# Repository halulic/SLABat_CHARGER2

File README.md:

Overview

This project is a smart charger for 12V SLA (Sealed Lead-Acid) batteries based on the ESP32 microcontroller.

The system monitors battery voltage, charging current, power, and temperature in real time and displays all important parameters on a TFT display.
Charging is controlled automatically to ensure safe and reliable battery charging.

⸻

Main Features
	•	Smart charging control for 12V SLA batteries
	•	ESP32 microcontroller
	•	Real-time monitoring of:
	•	Battery voltage
	•	Charging current
	•	Power consumption
	•	Temperature
	•	TFT display interface
	•	Automatic charge management
	•	MOSFET-based power control
	•	Protection and status indicators

⸻

Hardware

Main components used:
	•	ESP32 development board
	•	INA219 current/voltage sensors
	•	TFT display (ILI9341 / 3.2”)
	•	MOSFET switching stage
	•	NTC temperature sensor
	•	External power supply
	•	12V SLA battery

⸻

Display Information

The TFT display shows:
	•	Battery voltage
	•	Charging current
	•	Charging power
	•	Temperature
	•	Charging status
	•	System indicators

⸻

Applications
	•	Charging sealed lead-acid batteries
	•	Workshop battery maintenance
	•	DIY power electronics projects
	•	Educational electronics projects

⸻

Future Improvements

Possible future upgrades:
	•	Data logging
	•	WiFi monitoring
	•	Battery health estimation
	•	Charge cycle history

⸻

License

Open-source project for educational and DIY use.

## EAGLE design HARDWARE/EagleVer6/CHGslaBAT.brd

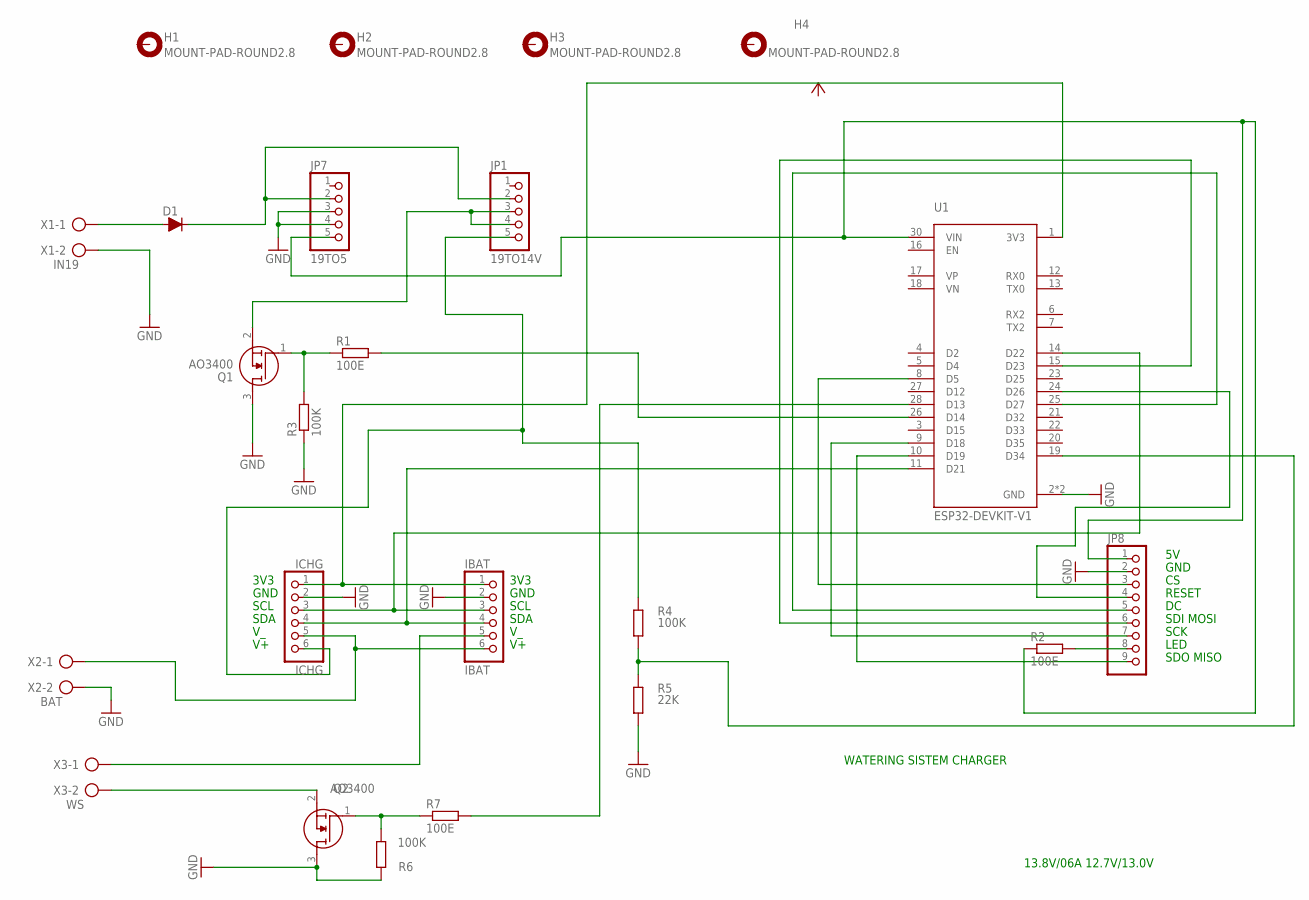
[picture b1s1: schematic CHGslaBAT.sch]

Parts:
D1: D-FILL-SOD-80; SOD80
H1, H2, H3, H4: MOUNT-PAD-ROUND2.8; 2,8-PAD
IBAT: IBAT; 1X06
ICHG: ICHG; 1X06
JP1: 19TO14V; 1X05
JP7: 19TO5; 1X05
JP8: PINHD-1X9; 1X09
Q1, Q2: AO3400; SOT95P280X125-3N
R1, R2, R7: 100E; M0805
R3, R4, R6: 100K; M0805
R5: 22K; M0805
U1: ESP32-DEVKIT-V1; MODULE_ESP32_DEVKIT_V1
X1: IN19; AK300/2
X2: BAT; AK300/2
X3: WS; AK300/2

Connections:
GND: IBAT.2, ICHG.2, JP7.3, JP7.4, JP8.2, Q1.3 (D), Q2.3 (D), R3.1, R5.2, R6.1, U1.2 (GND), U1.29 (GND), X1.2, X2.2
unnamed: D1.2 (A), X1.1
unnamed: D1.1 (C), JP1.2, JP7.2
unnamed: JP8.3, U1.8 (D5)
unnamed: Q2.2 (S), X3.2
unnamed: ICHG.6, JP1.5, R4.1
unnamed: Q1.1 (G), R1.1, R3.2
unnamed: IBAT.1, ICHG.1, U1.1 (3V3)
unnamed: IBAT.6, ICHG.5, X2.1
unnamed: IBAT.5, X3.1
unnamed: JP8.4, U1.24 (D26)
unnamed: JP8.8, R2.2
unnamed: JP8.5, U1.25 (D27)
unnamed: JP7.5, JP8.1, R2.1, U1.30 (VIN)
unnamed: IBAT.3, ICHG.3, U1.14 (D22)
unnamed: JP8.6, U1.15 (D23)
unnamed: JP8.7, U1.9 (D18)
unnamed: JP8.9, U1.10 (D19)
unnamed: R1.2, U1.26 (D14)
unnamed: IBAT.4, ICHG.4, U1.11 (D21)
unnamed: JP1.3, JP1.4, Q1.2 (S)
unnamed: R4.2, R5.1, U1.19 (D34)
unnamed: Q2.1 (G), R6.2, R7.1
unnamed: R7.2, U1.28 (D13)

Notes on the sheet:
GND
SCL
SDA
3V3
RESET
SDI MOSI
SCK
LED
SDO MISO
WATERING SISTEM CHARGER
13.8V/06A 12.7V/13.0V

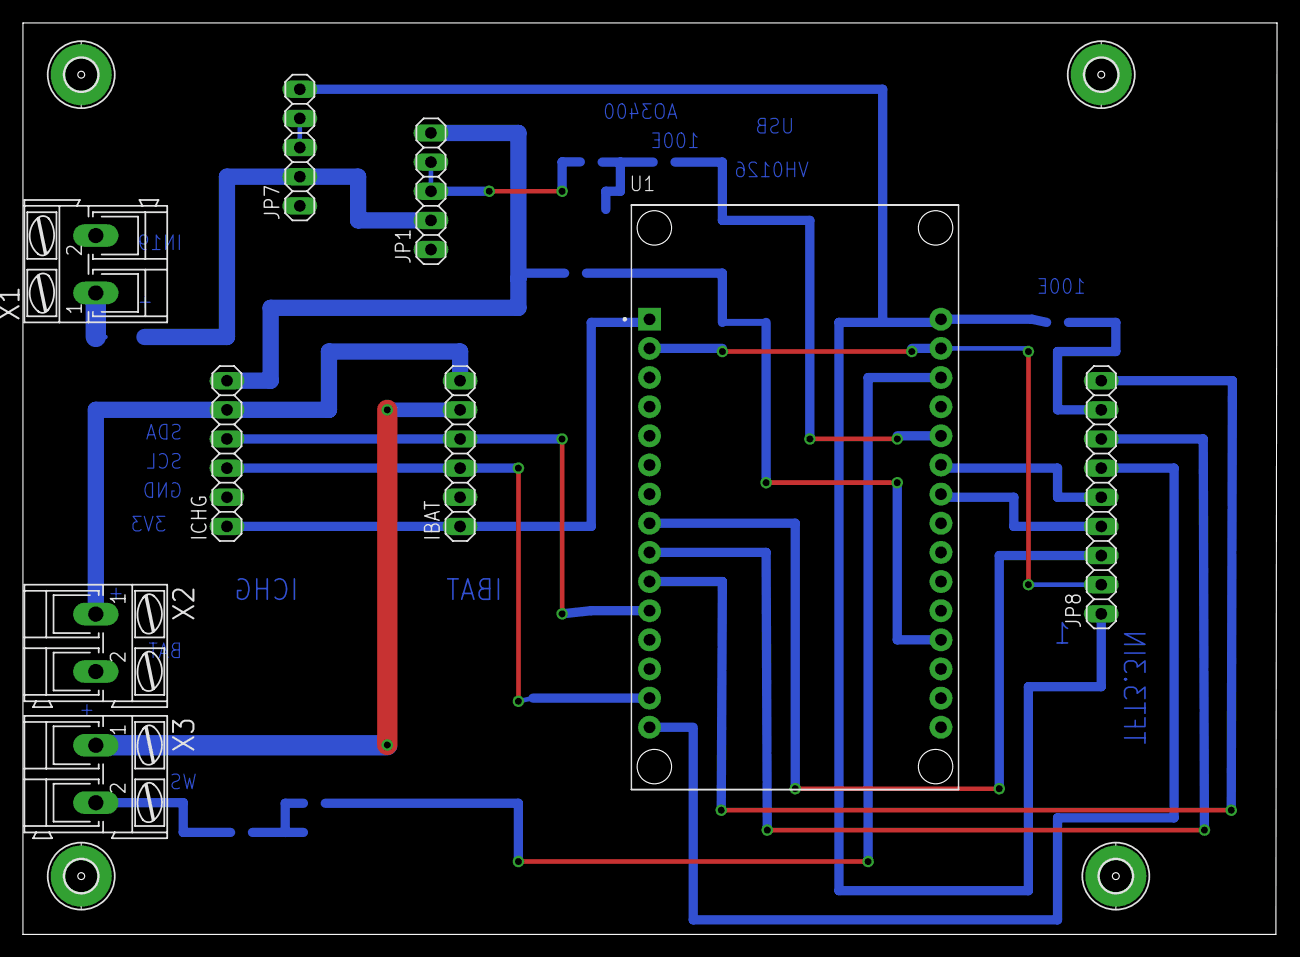
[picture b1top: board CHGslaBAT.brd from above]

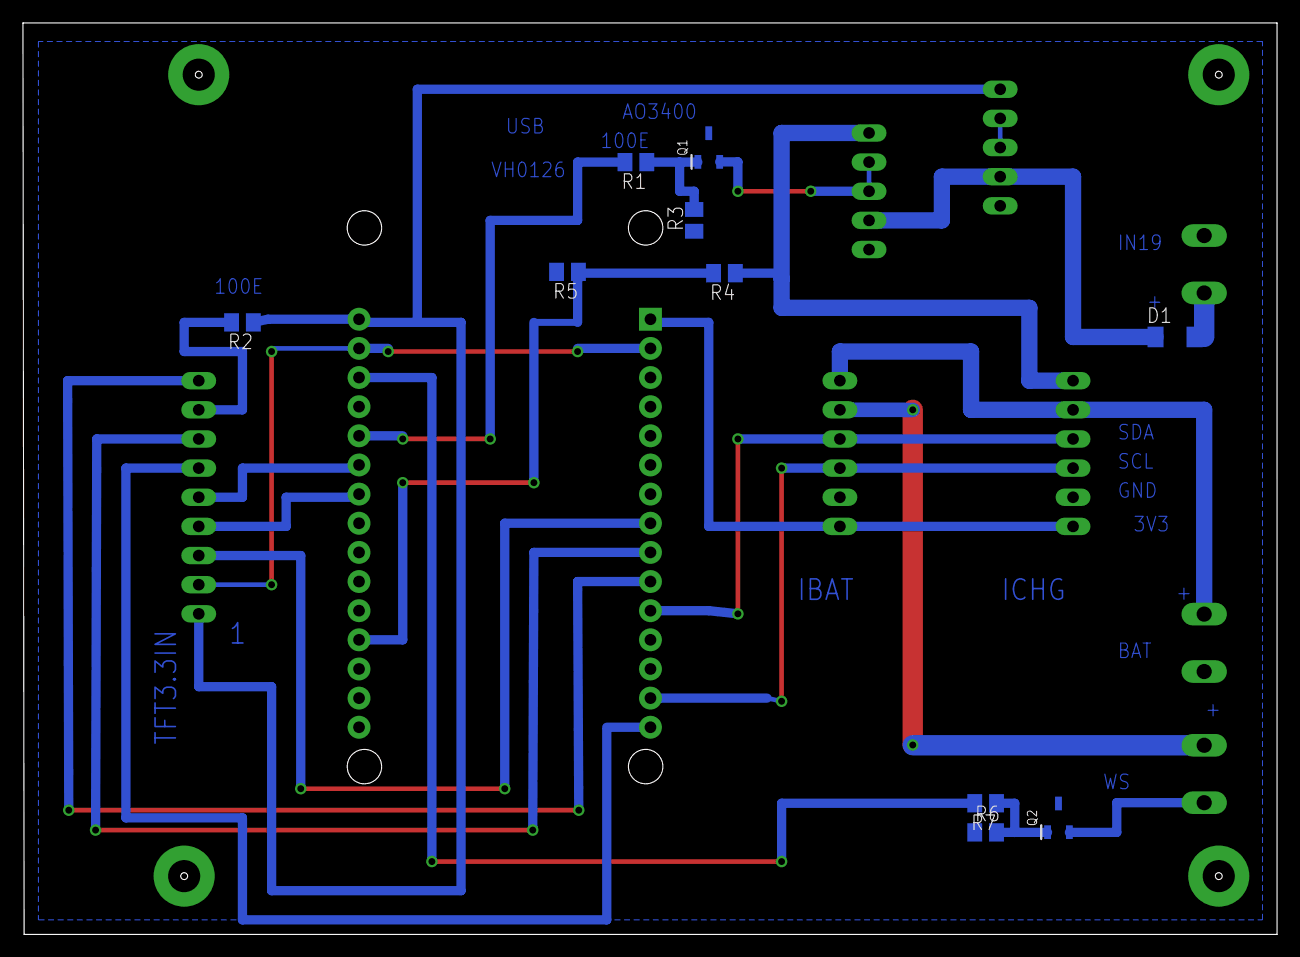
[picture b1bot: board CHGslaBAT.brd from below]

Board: 2 copper layers, 109.3 x 79.4 mm, 23 parts (10 on the bottom side), 24 nets.

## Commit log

2026-03-12 Add project overview and details to README
    This README provides an overview of the smart charger project, including its features, hardware components, display information, applications, and future improvements.
